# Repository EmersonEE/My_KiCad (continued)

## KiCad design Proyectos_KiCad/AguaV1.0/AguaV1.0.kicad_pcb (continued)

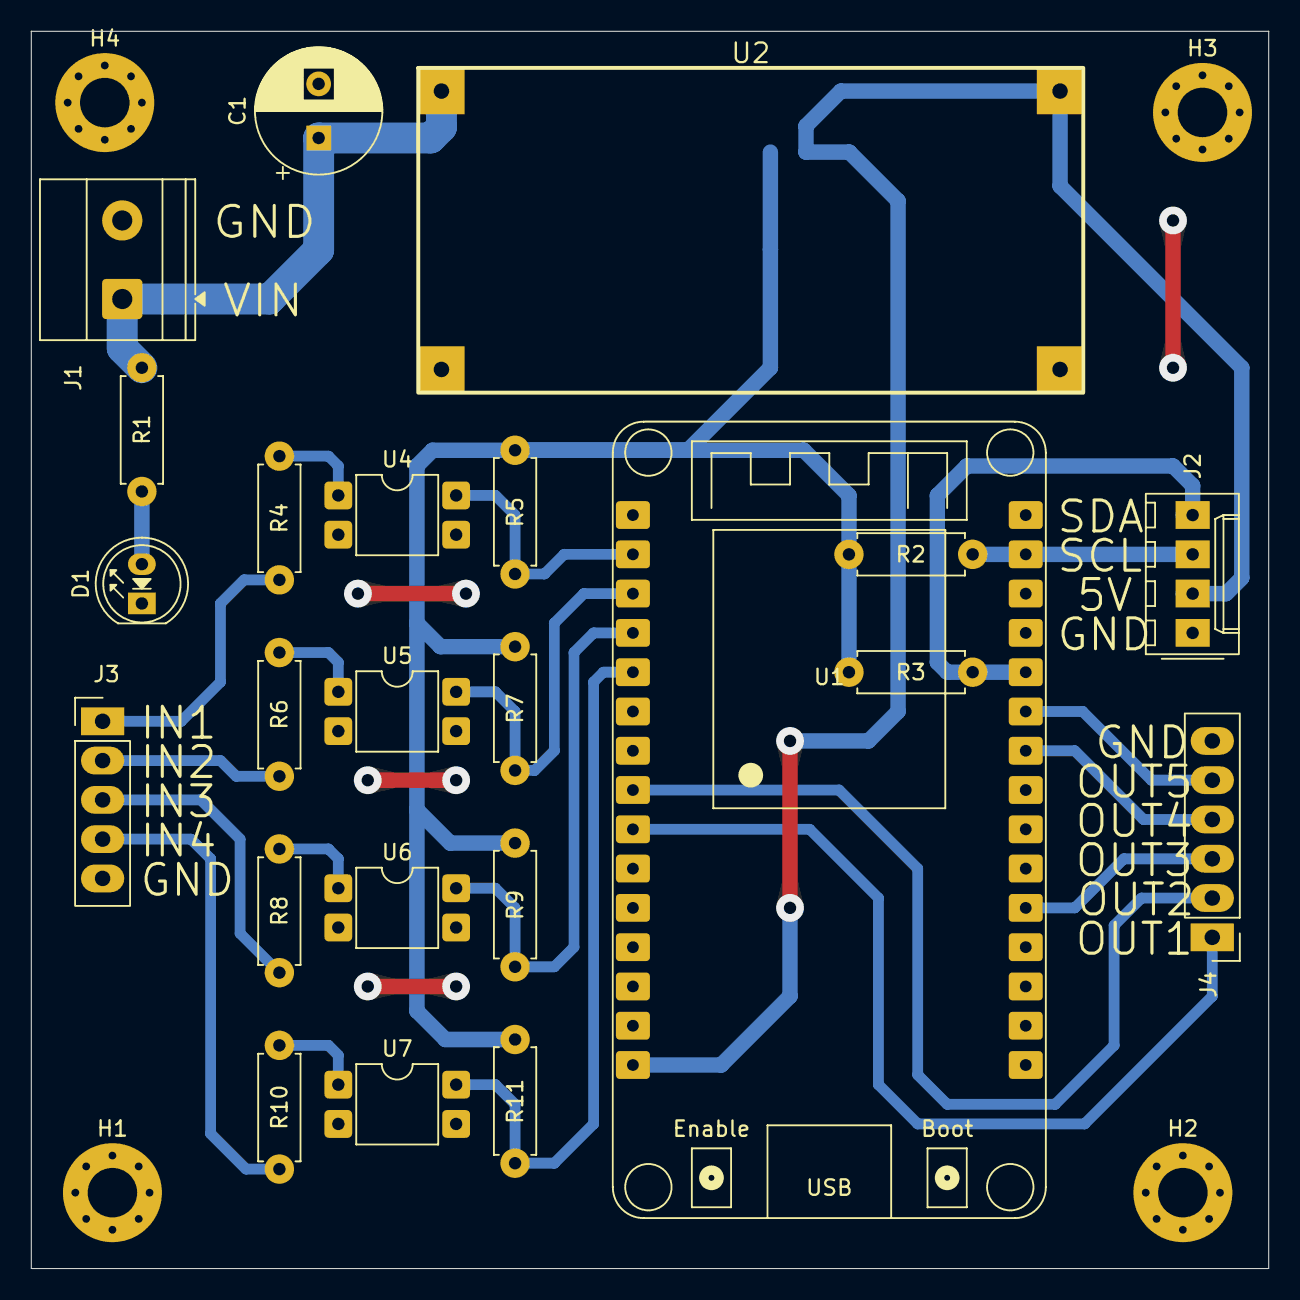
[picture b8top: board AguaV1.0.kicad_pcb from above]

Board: 2 copper layers, 80.0 x 80.0 mm, 28 parts (1 on the bottom side), 24 nets.
